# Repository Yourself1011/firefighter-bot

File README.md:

# Firefighter Bot

it fights fire

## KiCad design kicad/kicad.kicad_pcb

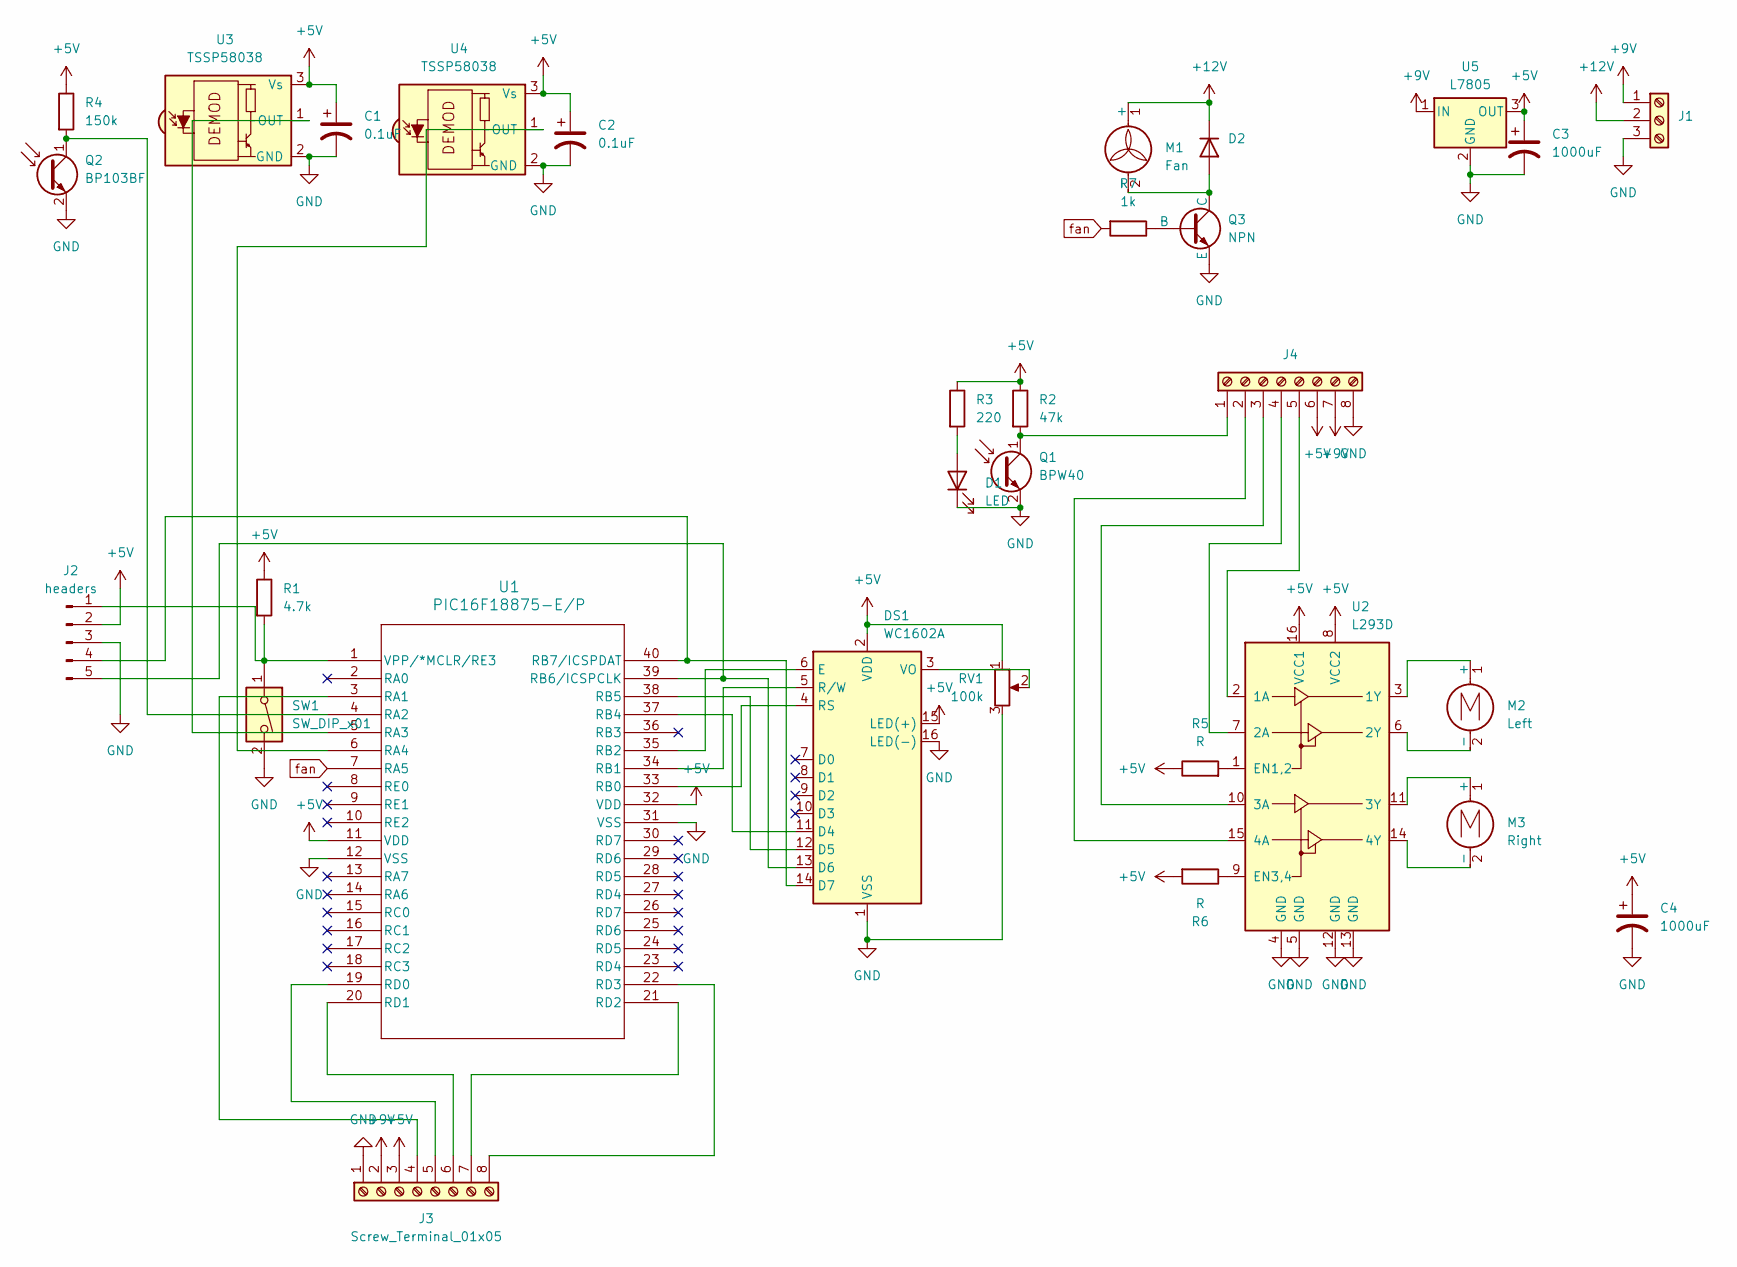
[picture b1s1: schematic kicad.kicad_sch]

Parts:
C1, C2: 0.1uF; C_Disc_D4.3mm_W1.9mm_P5.00mm
C3, C4: 1000uF; CP_Radial_D8.0mm_P3.80mm
D1: LED; SolderWire-0.5sqmm_1x02_P4.6mm_D0.9mm_OD2.1mm
D2: D; D_DO-41_SOD81_P7.62mm_Horizontal
DS1: WC1602A
J1: TerminalBlock_Phoenix_PT-1,5-3-5.0-H_1x03_P5.00mm_Horizontal
J2: headers; PinHeader_1x05_P2.54mm_Vertical
J3: Screw_Terminal_01x05; TerminalBlock_Phoenix_PT-1,5-8-5.0-H_1x08_P5.00mm_Horizontal
J4: TerminalBlock_Phoenix_PT-1,5-8-5.0-H_1x08_P5.00mm_Horizontal
M1: Fan; SolderWire-0.5sqmm_1x02_P4.6mm_D0.9mm_OD2.1mm
M2: Left; SolderWire-0.5sqmm_1x02_P4.6mm_D0.9mm_OD2.1mm
M3: Right; SolderWire-0.5sqmm_1x02_P4.6mm_D0.9mm_OD2.1mm
Q1: BPW40; SolderWire-0.5sqmm_1x02_P4.6mm_D0.9mm_OD2.1mm
Q2: BP103BF; SolderWire-0.5sqmm_1x02_P4.6mm_D0.9mm_OD2.1mm
Q3: NPN; TO-92_Inline_Wide
R1: 4.7k; R_Axial_DIN0207_L6.3mm_D2.5mm_P7.62mm_Horizontal
R2: 47k; R_Axial_DIN0207_L6.3mm_D2.5mm_P7.62mm_Horizontal
R3: 220; R_Axial_DIN0207_L6.3mm_D2.5mm_P7.62mm_Horizontal
R4: 150k; R_Axial_DIN0207_L6.3mm_D2.5mm_P7.62mm_Horizontal
R5, R6: R; R_Axial_DIN0207_L6.3mm_D2.5mm_P7.62mm_Horizontal
R7: 1k; R_Axial_DIN0207_L6.3mm_D2.5mm_P7.62mm_Horizontal
RV1: 100k; Potentiometer_Bourns_3386P_Vertical
SW1: SW_DIP_x01; SW_DIP_SPSTx01_Slide_9.78x4.72mm_W7.62mm_P2.54mm
U1: PIC16F18875-E/P; DIP-40_W15.24mm_LongPads
U2: L293D; DIP-16_W7.62mm
U3, U4: TSSP58038; SolderWire-0.5sqmm_1x03_P4.6mm_D0.9mm_OD2.1mm
U5: L7805; TO-220-3_Vertical

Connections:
+5V: C1.1, C2.1, C3.1, C4.1, DS1.2 (VDD), DS1.15 (LED(+)), J2.2, J3.3, J4.6, R1.1, R2.1, R3.1, R4.1, R5.1, R6.2, RV1.1, U1.11 (VDD), U1.32 (VDD), U2.8 (VCC2), U2.16 (VCC1), U3.3 (Vs), U4.3 (Vs), U5.3 (OUT)
+9V: J1.1, J3.2, J4.7, U5.1 (IN)
+12V: D2.1 (K), J1.2, M1.1 (+)
GND: C1.2, C2.2, C3.2, C4.2, D1.1 (K), DS1.1 (VSS), DS1.16 (LED(-)), J1.3, J2.3, J3.1, J4.8, Q1.2 (E), Q2.2 (E), Q3.3 (E), RV1.3, SW1.2, U1.12 (VSS), U1.31 (VSS), U2.4 (GND), U2.5 (GND), U2.12 (GND), U2.13 (GND), U3.2 (GND), U4.2 (GND), U5.2 (GND)
unnamed: D1.2 (A), R3.2
unnamed: D2.2 (A), M1.2 (-), Q3.1 (C)
unnamed: DS1.11 (D4), U1.37 (RB4)
unnamed: DS1.12 (D5), U1.38 (RB5)
unnamed: DS1.13 (D6), J2.5, U1.39 (RB6/ICSPCLK)
unnamed: DS1.14 (D7), J2.4, U1.40 (RB7/ICSPDAT)
unnamed: DS1.6 (E), U1.35 (RB2)
unnamed: DS1.4 (RS), U1.33 (RB0)
unnamed: DS1.5 (R/W), U1.34 (RB1)
unnamed: DS1.3 (VO), RV1.2
unnamed: J2.1, R1.2, SW1.1, U1.1 (VPP/*MCLR/RE3)
unnamed: J3.4, U1.3 (RA1)
unnamed: J3.5, U1.19 (RD0)
unnamed: J3.6, U1.20 (RD1)
unnamed: J3.7, U1.21 (RD2)
unnamed: J3.8, U1.22 (RD3)
unnamed: J4.1, Q1.1 (C), R2.2
unnamed: J4.2, U2.15 (4A)
unnamed: J4.3, U2.10 (3A)
unnamed: J4.4, U2.7 (2A)
unnamed: J4.5, U2.2 (1A)
unnamed: M2.1 (+), U2.3 (1Y)
unnamed: M2.2 (-), U2.6 (2Y)
unnamed: M3.1 (+), U2.11 (3Y)
unnamed: M3.2 (-), U2.14 (4Y)
unnamed: Q2.1 (C), R4.2, U1.4 (RA2)
unnamed: Q3.2 (B), R7.1
unnamed: U1.5 (RA3), U3.1 (OUT)
unnamed: U1.6 (RA4), U4.1 (OUT)
unnamed: R5.2, U2.1 (EN1,2)
unnamed: R6.1, U2.9 (EN3,4)
fan: R7.2, U1.7 (RA5)

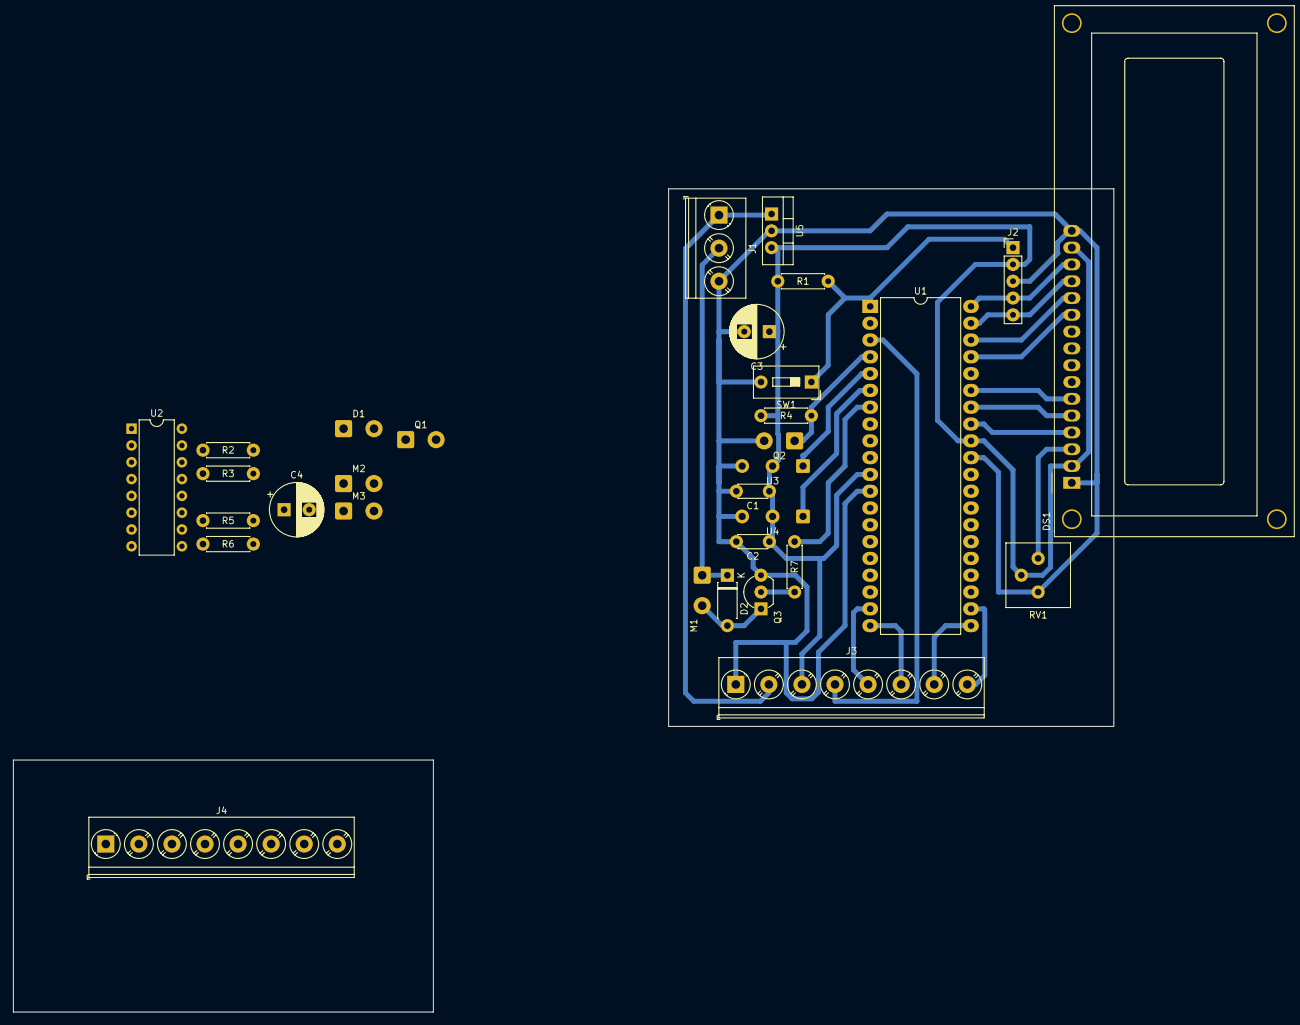
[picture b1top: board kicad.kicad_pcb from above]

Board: 2 copper layers, 166.4 x 124.5 mm, 31 parts (0 on the bottom side), 36 nets.

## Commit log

2025-02-24 led flash
2025-02-25 kicad
2025-03-03 line detection
2025-03-03 fix bug
2025-03-17 start kicad
2025-03-18 finished schematic
2025-03-18 linked all footprints
2025-03-19 components
2025-03-19 change pads
2025-03-19 upper board
2025-03-19 render pcb in readme
2025-03-19 update upload pages artifact version
2025-03-19 change pcb file name
2025-03-19 maybe quitting kicad will work
2025-03-19 update path again
2025-03-19 update deploy-pages version
2025-04-18 scheduling system
2025-04-29 maze 1 initial code
2025-04-29 kjhkj
2025-05-06 cooler turning
2025-05-06 clean up
    j
2025-05-06 alskdjflksdfj
2025-05-15 maze 1
